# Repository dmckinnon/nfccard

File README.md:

# NFC Card
Full project concept write up is [here](https://dmckinnon.github.io/NFC-Card/), but I'll repeat it below. 

Currently this repo just has the circuit; I've not written the code yet, a lot of the circuit needs to be tested first. This was developed with KiCad, and fabricated with [PCBWay](www.pcbway.com). This was a really easy and smooth experience, and if you want to try this circuit yourself I definitely recommend their services.

<br>
# Batteryless NFC Experiment
I like the idea of business cards that make a point through their existence (like mine, TODO link), but one problem I've had is that of power: these boards need to be powered by USB, or battery. Batteries are bulky or at least take up a lot of surface area. USB can be pretty compact – a 0.8mm board can slot into a USB-C cable, and for those who say "oh yes let's just plug this unknown circuit board into my laptop" 

ahem:

Use a USB wall power source.  

<br>

But this card still fundamentally requires an external power source of some sort. Wouldn't it be nice to do away with that entirely? 

There are several ways we could achieve this. Solar, for example. Thermal energy. Mechanical energy, although this would require a number of moving parts, whereas solar and thermal can be solid state. What these all share, however, for the application of a business card is that each would provide so little energy per unit time that we need to accumulate the energy, store it, and then expend it in a burst.  
 
That's actually ok! The speech recognition business card I made is used in a bursty fashion, meaning it's powered up, used briefly, and spends most of its time being off. Using energy-storing supercapacitors, we can slowly store energy, and then burn it all on the card's demonstration circuit.  

<br>

## Contents
- [The Idea](#the-idea) 
- [Energy Considerations](#energy-considerations)
- [The Circuit](#the-circuit)
- [Fabrication](#fabrication)

<br>

## The Idea
It's all well and good to have a card with _my_ details on it, but this is of no use to you. What if you could rewrite this to have your details? Contacts are frequently shared with NFC today – Near Field Contact – using RF waves. I want to have a card that one can display their own details on.  

In keeping with the theme above, we want this to be batteryless, and therefore consume no passive power; it should only use energy when updating. There are two key usage elements here: 

1. Writing to the card with NFC 

2. Displaying this new information 

For the first, this gives us our power solution. Several NFC chips exist with an energy harvesting option, whereby the energy in the RF waves that contain the signal is also collected and stored, via induction through the NFC coils. Excellent! We feed this into a super capacitor, and with some extra circuitry, can make this fire up a chip when we have enough energy.  

For the second, we want this displaying constantly – no use flashing information for 0.1s. Thankfully, eInk displays solve this one. They cost more energy per pixel to change than an OLED display, but crucially cost no energy to continue displaying – only change costs energy.  

The usage is then: phone sends information via NFC, and stays within range long enough to transmit enough power. Supercapacitor charges up from this, and when a chip measuring the capacitor hits a limit it opens, and sends a regulated flow of energy through to the main microcontroller. Microcontroller boots in low power mode, reads data from NFC chip, writes to the display (main energy user), and then safely powers down. Display has updated with new information.  

<br>

## Energy considerations 

We have to power a microcontroller and the NFC chip long enough to read the message, and then the microcontroller and the eInk display, long enough to update the display. Eyeballing things, since I have no code yet, this should take not more than maybe 100-150ms. Microcontrollers are well-optimised for low-power use cases, so this can be pretty negligible (ditto the NFC chip), so our main concern is the eInk display refresh power usage.

The discussion below on the [supercapacitor](#supercap) will detail the energy we can store, and the discussion about the [eInk display](#the-eink-display) will detail the energy requirements in greater depth. 

<br> 

## The circuit 

This circuit has a lot of parts each with a necessary job. I'll show the flow of energy and information, and go over each part. The basic flow is:

NFC antenna -> NFC chip -> supercap -> load switch -> LDO -> buck-boost/regulator -> microcontroller -> eInk 

<br>

### NFC Antenna and chip 

There are two main parts to discuss: U1, the NFC chip, and AE1, the antenna. Everything else is either passive and assistive components, or it actually just got caught in the screenshot and will be discussed next (ahem C1 on the right).  

The NFC antenna was designed with a [generator script](https://github.com/nideri/nfc_antenna_generator) and requires a certain geometry, number of loops, etc to work with the frequency, energy transmission, and guarding against interference. I've never done antenna work before, so there's a lot of uncertainty around this. 

Some of the factors are:
- antenna area: more area means more magnetic flux captured, therefore more power harvested
- number of turns: increases induced voltage and inductance, but also increases resistance
- trace width: wider means lower resistance, generally better efficiency
- spacing: affects inductance, parasitic capacitance, and coupling between turns
- inductance of overal antenna: must work with the NFC chip's internal capacitance to hit resonance (can tune this with components)

Essentially, there's a certain amount of 'tuning' that goes into getting a custom antenna right. Physical characteristics that are baked in, like width, could be countered by capacitors across the antenna, but this whole ordeal likely requires a number of board iterations. One major heuristic I'm working from is to maximise antenna area (given the constraint I've placed upon board size of "business card footprint"). We further tune according to the chip's datasheet, which leads us to ...

The [ST25DV64K](datasheet), a standard NFC chip, has 64K of internal flash to store transmitted data – gross overkill as the messages will be small – and an energy harvesting mode. This circuit includes an external power method, so I can do setup work, but the final product will start in energy-harvesting mode. Energy collected by the antenna will be funneled through the rest of the circuit (see below) and when this is enough, will power the VCC and GND rails and the rest of the chip will activate. Then the ST25 can read the NFC data being sent, and communicate this to the microcontroller via I2C in the SDA and SCL lines on the left.  

Back to combining this with the antenna, the datasheet for the ST25D specifies that the internal tuning capacitance is $C=28.5pF$. The NFC RF frequency is 13.56MHz, and theerfore we need an antenna with an inductance of approximately $L=4.8\mu H$, as per

$f = \frac{1}{2\pi \sqrt{LC}}$

So we'll need to tune the antenna's inductance towards that. 

Next, there is the question of power draw from the antenna through the chip. The current is a function of the magnetic field strength, and the datasheet provides some tested levels, including ~0.7mA at 3.3v. Using 

$E = VCt$

where $E$ is energy, $V$ is voltage, $C$ is current and $t$ is time, the charge time we'll need to accumulate ~40mJ (see [Supercap](#supercap) discussion below for how we get this number) is 

$t = \frac{0.04}{3.3\times0.0007}=17s$

Which is a long time to be holding a phone and doing NFC. The datasheet does have different datapoints, for example 4.5mA at 2.57V, and like I said above there's some experimentation to do with the antenna, but this isn't looking great.

<br>

### Supercap 

Capacitors are a deep and complex component, but given that we are talking about DC, we can ignore a considerable amount of that. For the usage here, all we need is that a capacitor stores electrical energy. In digital circuits, capacitors typically range from 100 picoFarads to perhaps 5 microFarads, and the use case is smoothing out fluctuations in voltage – since they have energy stored, if the voltage supply dips they can suddenly produce energy to cover that dip, and if it spikes they can absorb the spike.

This capacitor, however, is in the milliFarad range, and that's enormous. The purpose here, as we know, is to store all the incoming energy from NFC, and then when some future circuit element decides its time, to let this loose and power the rest of the circuit, draining entirely in the process. A battery, of sorts.  

If we have 10mF, and discharge from 4v to 2.8v we have  
$E = \frac{1}{2}C(V_{hi}^2 – V_{lo}^2) = 0.0408J$ 

So we have about 40 milliJoules to play with. As mentioned in the [Antenna](#nfc-antenna-and-chip) discussion above, this requires considerable charge time. 

<br>

### Voltage Supervisor 

The element in question here is U2, a voltage supervisor. This reads the supercapacitor voltage as it charges and will activate its RESET signal when the voltage is high enough.  

Why is this necessary? We could simply let the circuit activate itself when the cap has enough energy stored; after all, a low enough voltage won't activate the circuit.  

However, such a setup would mean that it would activate at the minimum level, and then run out soon after. This allows us to set a higher level, and only activate when we have not just the minimum, but the sufficient energy. Furthermore, it has built-in hysteresis so that brief voltage spikes do not activate the circuit unnecessarily. It will only activate under a consistent reliable load. 

<br>

### Load Switch 

U5 is the load switch, and I include the voltage supervisor so we can see how it feeds into the load switch. A load switch is, at its most basic, a signal-triggered switch. While there is current control, etc, the main feature we care about is this circuit isolation and switching behaviour. When the supervisor detects enough energy to power the circuit for the time we need, it will send a signal to the load switch, which activates and allows current to flow through. The supervisor also manages a stable deactivation, shutting down when the voltage from the cap is too low – this avoids unstable brown-out behaviour. The capacitor C3 on the right helps stabilise the current on the output.

<br>

### Buck-boost converter 

Now that we actually have a power flow, we need to regulate it. I could use a linear 3.3v regulator, but a) those aren't particularly efficient, and b) if the incoming power line drops below 3.3v, a regulator cannot bring it back up. A buck-boost can. It'll be more power hungry, but that might be necessary to buy another 50ms or whatever is needed. I originally had a Low Drop Out regulator, to cut off when power got low, but for the initial design I'm going with buck boost – to maintain stable power.  This particular module boasts 90% efficiency up to half an amp of throughput, which is far higher than we're ever going to go. 

That's power sorted! 

<br> 

### Microcontroller 

The microcontroller assumes a steady power for the duration of the program necessary. For prototyping, I'm using an external power source anyway, that won't run out, so no stress there. For actual runtime … this is where some level of experimentation comes in. I've run the numbers, and I think it will last. 

I'm using the STM32L031 processor – a 32-bit chip designed for low power use cases. Once everything is powered, the intended program is, on a high level: 

1. using I2C protocol (pints 17 and 18, lower right), request the NFC message from the ST25D chip (which, being stably powered itself, will have received) 

2. Using SPI protocol (pins 9, 10, 11, 12, right middle), and a graphics library, write the text of this message to the eInk display 

3. Power down into sleep mode gracefully (honestly, this isn't strictly necessary)

There is an LED on pin 6 for testing – an LED can be pretty low power, and if I can get it to flash in a certain way, that can indicate reaching a certain part of the program for debugging purposes.  

The rest of the circuitry here is for programming mode or reset mode (the switches on the left). 

As for power usage, this draws ~2.4mA at 32MHz (that is, we could boost it up to a higher processing frequency … but simply don't need to. At 50-150ms, we're drawing negligible current). This is negligible next to the eInk display, so we'll ignore it. If you want the actual numbers, energy is voltage times current times time:

$E = V \times C \times t = 3.3v \times 0.0024 \times 0.15 = 1.1mJ$

<br>

### The eInk display 

This is not actually part of the initial design! I've set some breakout pins for the communication and power, and will hold the screen externally for now.  

Tp update the Waveshare 1.54" eInk display, the [datasheet](https://files.waveshare.com/upload/e/e5/1.54inch_e-paper_V2_Datasheet.pdf) reports a maximum of 8 mAs - 8 milliamp-seconds. Energy is voltage times charge, where charge is current by time, we get  
$E = V \times C \times 1s$ 

$= 3.3v \times 0.008 \times 1$ 

$= 26.4mJ$ 

This is the maximum energy required for a full screen update. We can optimise this by using a smaller display, or by just partially updating this display. If we update a fifth of the screen, we can use ~ a fifth the power, and achieve ~5mJ draw from the display.  

From [above](#supercap), we can store about 40mJ of energy. We're well within budget drawing 25, but I like to live on the safe side. This also means, if we can reduce energy budget, that we could also not charge for as long. [Recall](#nfc-antenna-and-chip) that charging to 40mJ could take ~17 seconds. If we charge to 5mJ + 1.1mJ, we're down to ~2.6s. 

<br>

### PCB layout 

It's tight! 

There's a major potential problem here. NFC is a radio-frequency electromagnetic signal, which induces current in anything metal. The small metal legs of compnents aren't much, but there's a lot of them, they're connected by traces, and NFC requires precision. What's even more alarming is the GND plane on the back layer, seen as the centre blue rectangle in the upper picture.  

Ground planes are a useful circuit feature for cleaning up noise and reducing stray capacitnacer (inductance?), so we want some level of GND plane, BUT … this also is ripe for allowing an opposing magnetic field that would affect the NFC signal. So there's a tension between making this as small as possible, but also having it still exist. Something to experiment with.  

"Couldn't the NFC antenna be off to one side, with no components inside?" 
Yes, this is entirely possible.  

However, this affects the energy we can capture - as discussed in the [antenna section](#nfc-antenna-and-chip), antenna area is proportional to power captured, and I want to maximise this per unit time. 

<br>

## Fabrication 

I can hum and haw and calculate away until the cows come home – or until I purchase some cows – but all of that is meaningless if I don't actually try. To get it fabricated, I'm using [PCBWay](https://www.pcbway.com/). I've used them before, it's a really easy and affordable service and I've had a great experience.  

To [get a quote](https://www.pcbway.com/orderonline.aspx), you give basic info like dimensions, # of layers, colour (we're going blue for this one), and you get a ballpark price then and there: 

Afdter [exporting and uploading all necessary files from KiCad](https://www.pcbway.com/blog/PCB_Design_Tutorial/How_to_Export_Gerber_and_Production_Files_in_KiCad.html) (which is really easy and they document how to do it), one of their technicians will take a look – on previous projects I've had some back and forth about some parameters or errors that I'm glad they found.  

Once all that is sorted out, it gets fabricated and shipped, and a ride across the Pacific later (for me) it's at your door. For parts I go Mouser or Digikey, and of course if you don't want to solder parts yourself PCBWay also has the option of [doing this for you as well](https://www.pcbway.com/quotesmt.aspx).

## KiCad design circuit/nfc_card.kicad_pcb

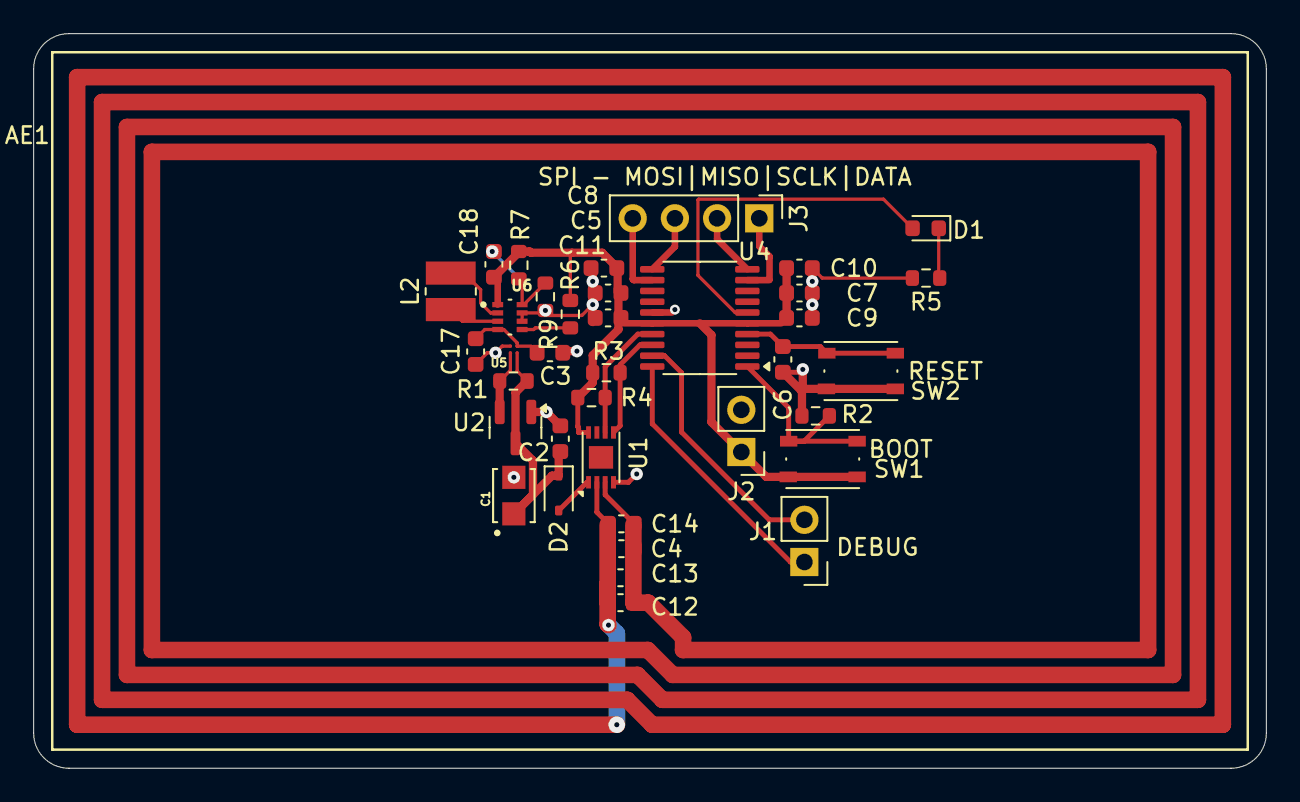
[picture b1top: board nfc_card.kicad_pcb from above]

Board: 2 copper layers, 74.2 x 44.2 mm, 38 parts (0 on the bottom side), 24 nets.

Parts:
AE1: Antenna_Loop; nfc_ant
C1: 10mF; CAPCP3225X100N
C2: 0.1uF; C_0603_1608Metric
C3, C4, C8, C12, C13, C14: 1uF; C_0603_1608Metric
C5: 10nF; C_0603_1608Metric
C6, C9, C10, C11: 100nF; C_0603_1608Metric
C7: 4.7uF; C_0603_1608Metric
C17: 22uF; C_0603_1608Metric
C18: 47uF; C_0603_1608Metric
D1: LED; LED_0603_1608Metric
D2: BAT60A; D_SOD-323
J1, J2: Conn_01x02_Pin; PinHeader_1x02_P2.54mm_Vertical
J3: Conn_01x04_Pin; PinHeader_1x04_P2.54mm_Vertical
L2: 1uH; L_Ferrocore_DLG-0302
R1, R2, R5: 10K; R_0603_1608Metric
R3, R4: 4.7K; R_0603_1608Metric
R6: 1k; R_0603_1608Metric
R7: 511; R_0603_1608Metric
R9: 91; R_0603_1608Metric
SW1, SW2: SW_Push; SW_Push_1P1T_NO_Vertical_Wuerth_434133025816
U1: ST25DV64K-IER8C3; DFN-8-1EP_3x2mm_P0.5mm_EP1.36x1.46mm
U2: TLV810EA29DBZ; SOT-23
U4: STM32L031F4Px; TSSOP-20_4.4x6.5mm_P0.65mm
U5: TPS22916BYFPT; BGA4C40P2X2_77X77X50
U6: TPS631000DRLR; SOT50P160X60-8N

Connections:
GND: C1.2, C2.1, C3.2, C5.2, C6.1, C7.2, C8.2, C9.2, C10.2, C11.2, C17.2, C18.1, J2.2, R2.2, R5.2, R9.2, SW2.1, U1.4 (VSS), U2.1 (GND), U4.15 (VSS), U5.B1 (GND), U6.6 (MODE), U6.7 (GND)
I2C_SCL: R4.2, U1.6 (SCL), U4.17 (PA9)
I2C_SDA: R3.2, U1.5 (SDA), U4.18 (PA10)
unnamed: D1.2 (A), U4.6 (PA0)
unnamed: D1.1 (K), R5.1
unnamed: D2.2 (A), U1.1 (V_EH)
unnamed: C1.1, C2.2, D2.1 (K), R1.1, U2.3 (V_{DD}), U5.A2 (VIN)
unnamed: AE1.1, C4.2, C12.2, C13.2, C14.2, U1.2 (AC0)
unnamed: AE1.2, C4.1, C12.1, C13.1, C14.1, U1.3 (AC1)
unnamed: R1.2, U2.2 (RESET), U5.B2 (ON)
unnamed: R2.1, SW1.2, U4.1 (BOOT0)
unnamed: C6.2, SW2.2, U4.4 (NRST)
unnamed: C3.1, C17.1, U5.A1 (VOUT), U6.4 (VIN)
unnamed: R6.1, U6.5 (EN)
unnamed: R7.2, R9.1, U6.8 (FB)
unnamed: L2.1, U6.3 (LX1)
unnamed: L2.2, U6.2 (LX2)
SPI_DATA: J3.1, U4.9 (PA3)
SPI_MISO: J3.3, U4.11 (PA5)
SPI_MOSI: J3.4, U4.12 (PA6)
SPI_SCLK: J3.2, U4.10 (PA4)
SWCLK: J1.1, U4.20 (PA14)
SWDIO: J1.2, U4.19 (PA13)
VDD: C5.1, C7.1, C8.1, C9.1, C10.1, C11.1, C18.2, J2.1, R3.1, R4.1, R6.2, R7.1, SW1.1, U1.8 (VCC), U4.5 (VDDA), U4.16 (VDD), U6.1 (VOUT)
